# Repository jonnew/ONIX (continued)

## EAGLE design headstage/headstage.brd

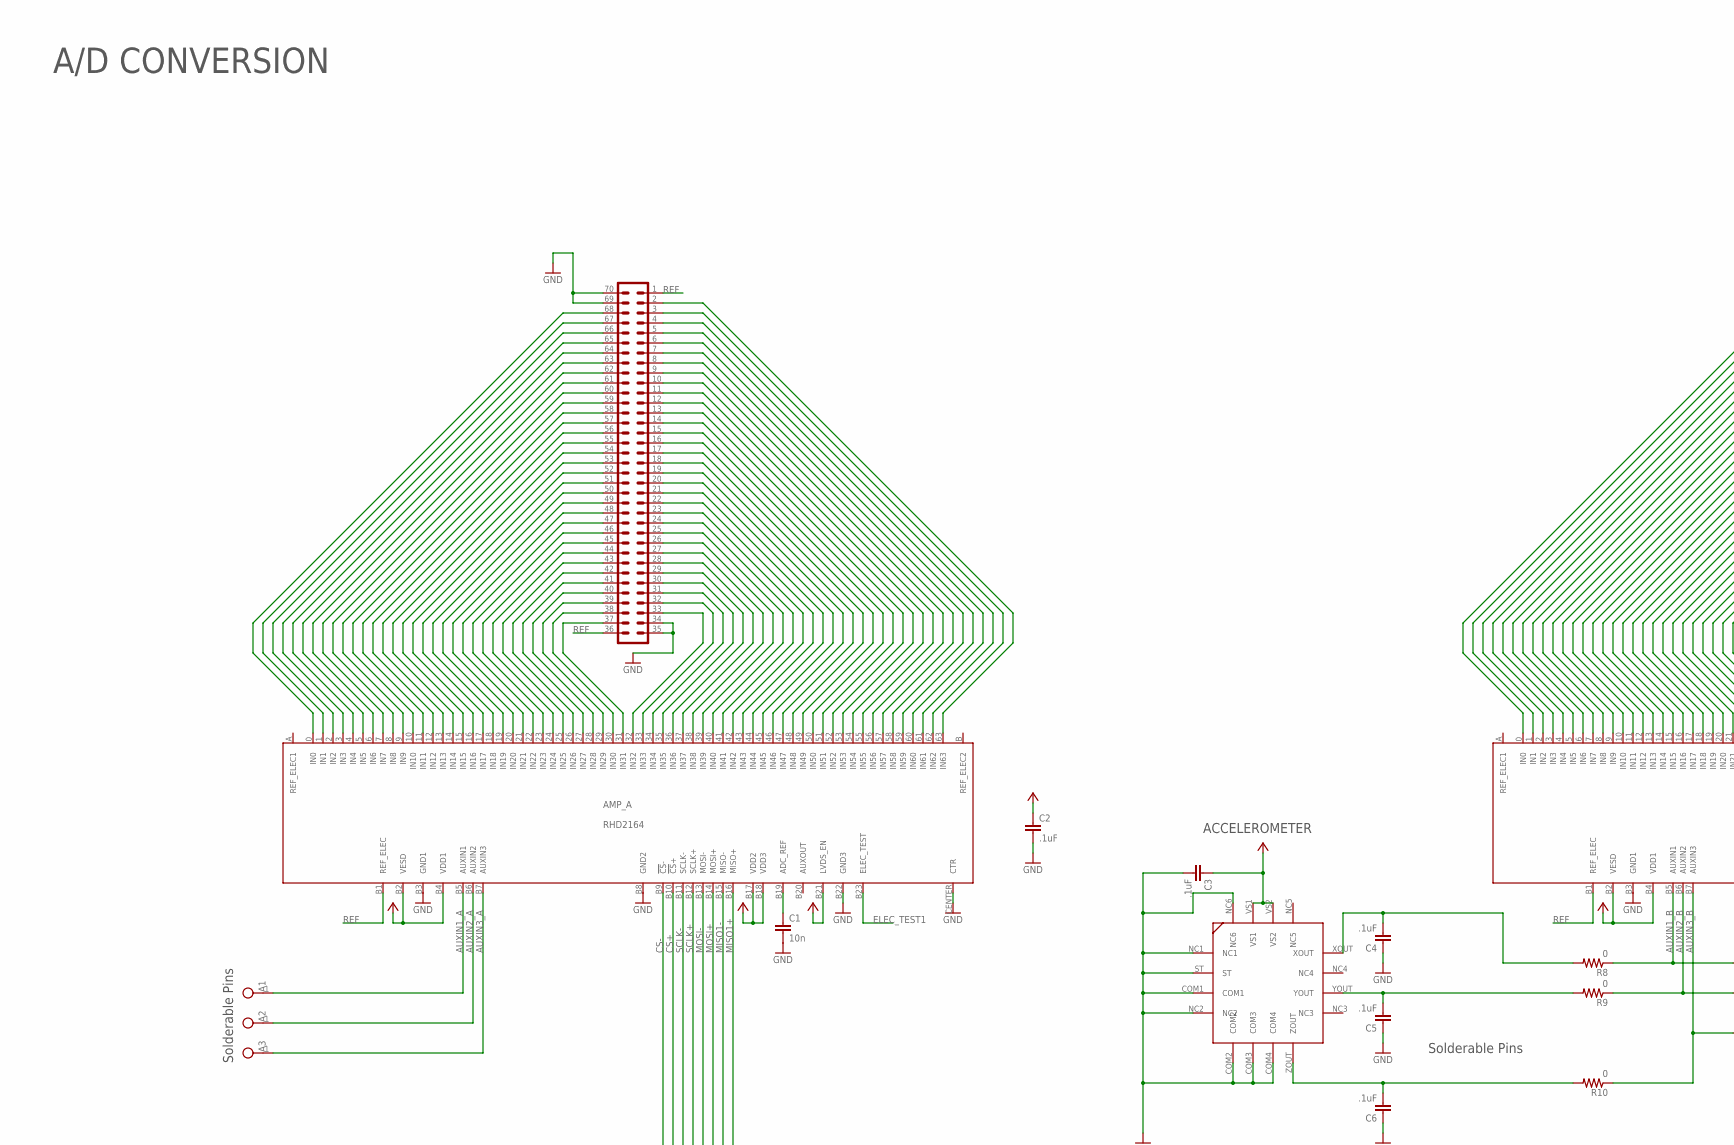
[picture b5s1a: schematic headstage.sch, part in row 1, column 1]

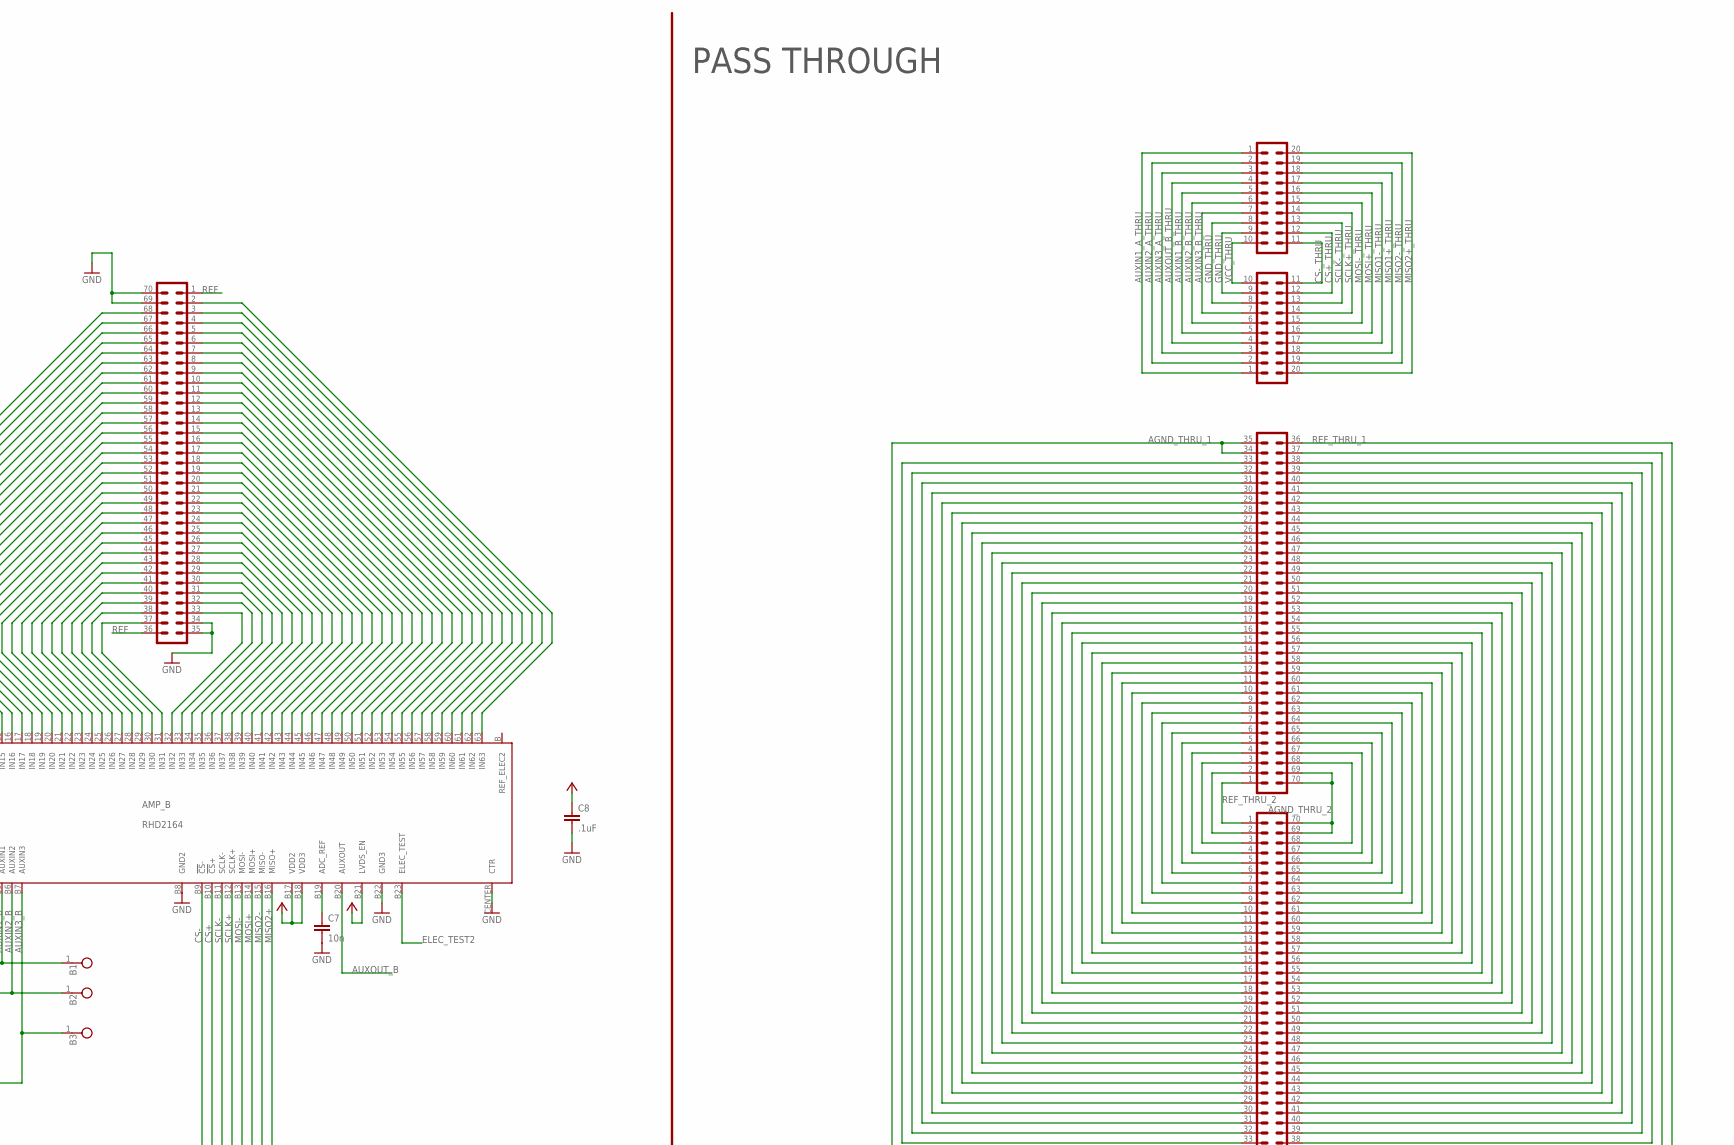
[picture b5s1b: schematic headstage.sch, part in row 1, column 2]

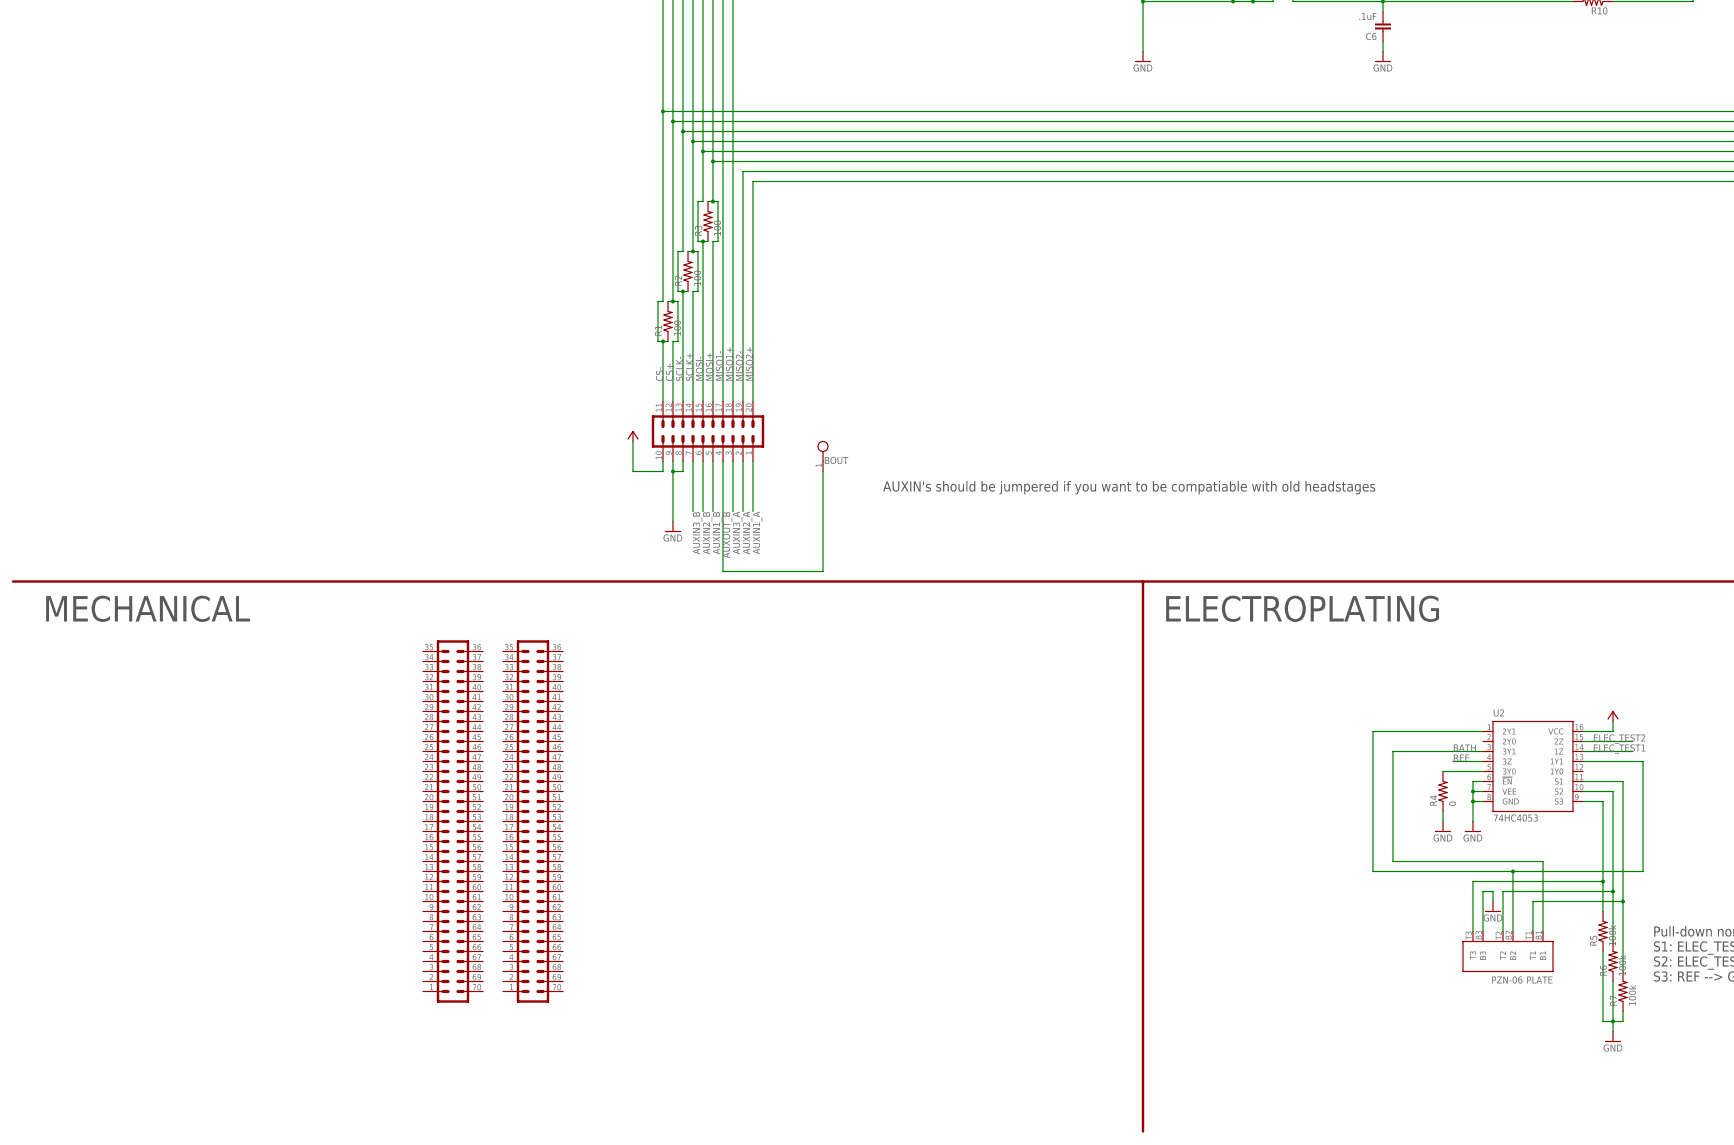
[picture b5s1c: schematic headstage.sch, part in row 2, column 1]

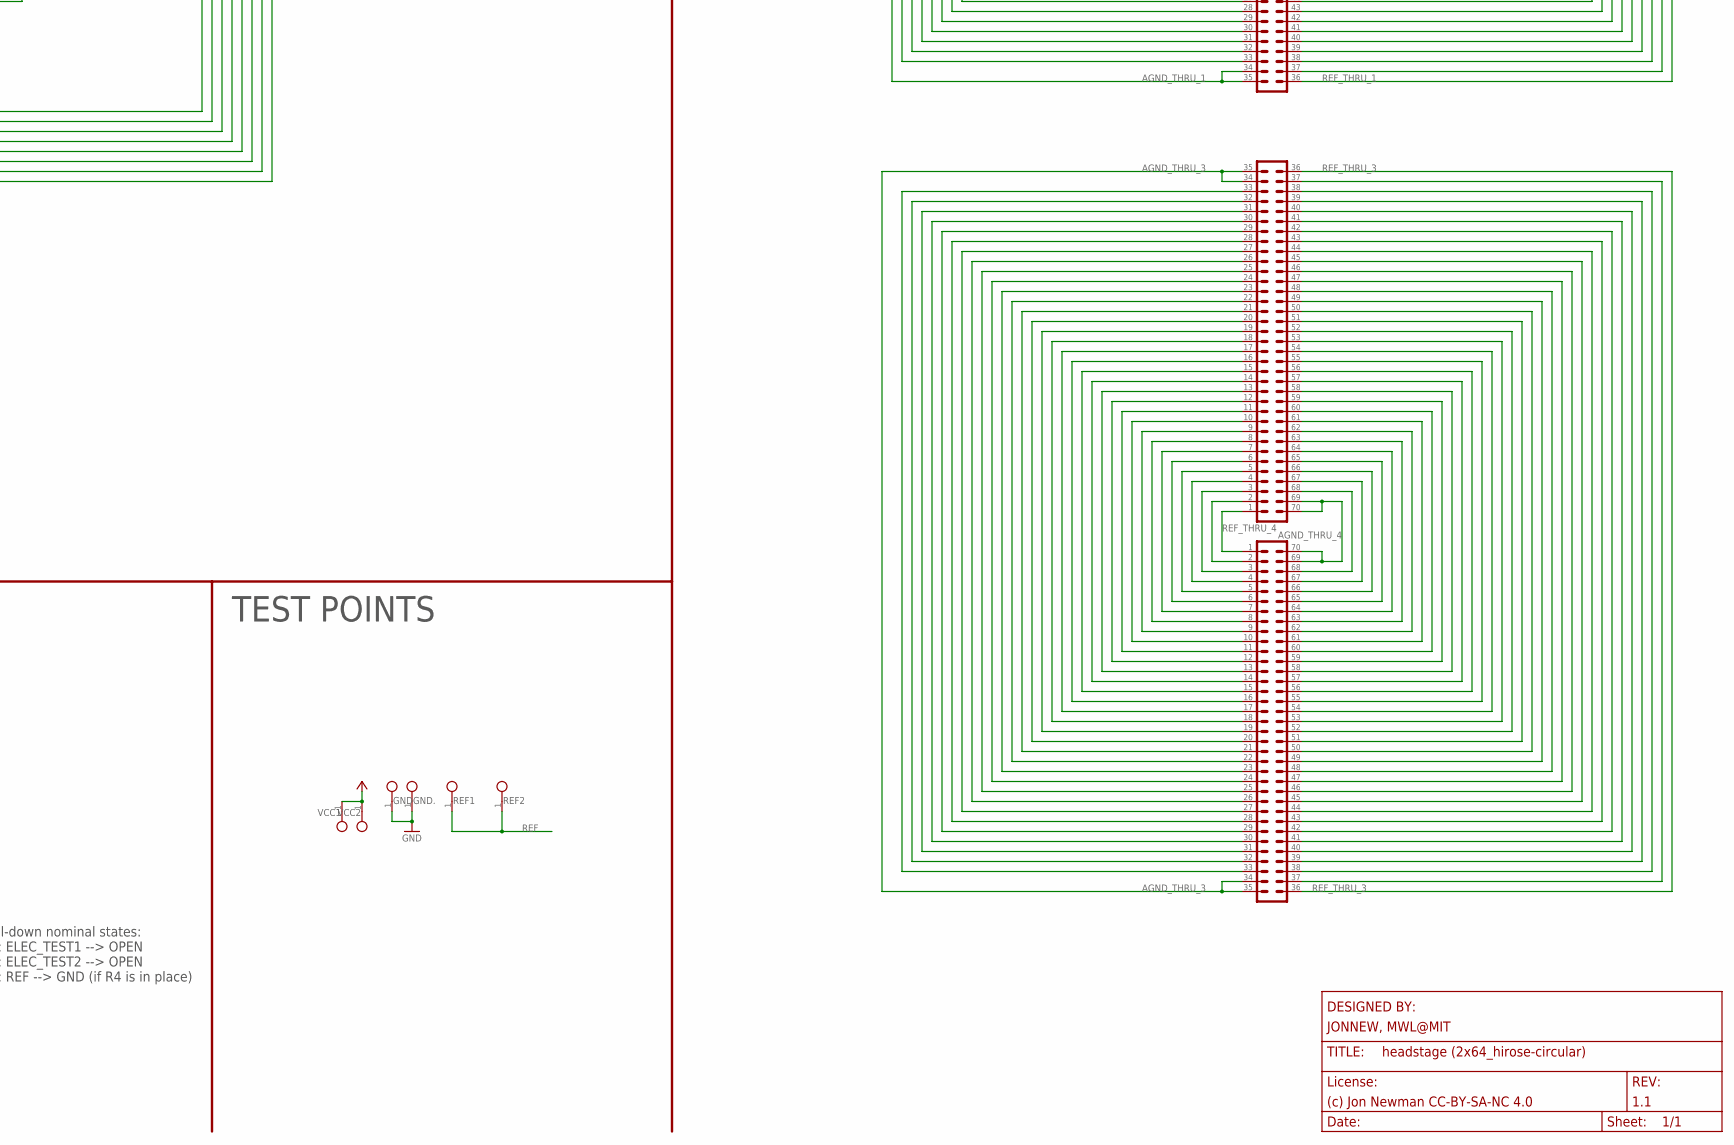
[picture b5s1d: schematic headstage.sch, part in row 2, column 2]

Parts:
A1, A2, A3: TESTPOINT_SMALL
AIN_BNB: DF40REC; DF40-70REC
AIN_BSB: DF40REC; DF40-70REC
AMP_A: RHD2164; RHD2164_COB
AMP_B: RHD2164; RHD2164_COB
ATHRU_BEB: DF40REC; DF40-70REC
ATHRU_BWB: DF40REC; DF40-70REC
ATHRU_TEB: DF40HEAD; DF40-70HEAD
ATHRU_TWB: DF40HEAD; DF40-70HEAD
B1, B2, B3: TESTPOINT_SMALL
BOUT: TESTPOINT_SMALL
C1, C7: 10n; 0201
C2, C3, C4, C5, C6, C8: .1uF; 0402
DIO_TEA: DF40HEAD; DF40-20HEAD
DTHRU_BNA: DF40REC; DF40-20REC
DTHRU_TNA: DF40HEAD; DF40-20HEAD
GND, GND.: GND; TESTPOINT_SMALL
MECH_TNB: DF40HEAD; DF40-70HEAD
MECH_TSB: DF40HEAD; DF40-70HEAD
PLATE: PZN-06; OMNETICS_PZN-06-AA
R1, R2, R3: 100; 0201
R4: 0; 0402
R5, R6, R7: 100k; 0201
R8, R9, R10: 0; 0201
REF1, REF2: REF; TESTPOINT_SMALL
U1: ADXL335
U2: 74HC4053; TSSOP-16
VCC1, VCC2: VCC; TESTPOINT_SMALL

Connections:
AGND_THRU_1: ATHRU_BWB.34, ATHRU_BWB.35, ATHRU_TWB.34, ATHRU_TWB.35
AGND_THRU_2: ATHRU_BWB.69, ATHRU_BWB.70, ATHRU_TWB.69, ATHRU_TWB.70
AGND_THRU_3: ATHRU_BEB.34, ATHRU_BEB.35, ATHRU_TEB.34, ATHRU_TEB.35
AGND_THRU_4: ATHRU_BEB.69, ATHRU_BEB.70, ATHRU_TEB.69, ATHRU_TEB.70
AUXIN1_A: A1.1, AMP_A.B5 (AUXIN1), DIO_TEA.1
AUXIN1_A_THRU: DTHRU_BNA.1, DTHRU_TNA.1
AUXIN1_B: AMP_B.B5 (AUXIN1), B1.1, DIO_TEA.5, R8.1
AUXIN1_B_THRU: DTHRU_BNA.5, DTHRU_TNA.5
AUXIN2_A: A2.1, AMP_A.B6 (AUXIN2), DIO_TEA.2
AUXIN2_A_THRU: DTHRU_BNA.2, DTHRU_TNA.2
AUXIN2_B: AMP_B.B6 (AUXIN2), B2.1, DIO_TEA.6, R9.1
AUXIN2_B_THRU: DTHRU_BNA.6, DTHRU_TNA.6
AUXIN3_A: A3.1, AMP_A.B7 (AUXIN3), DIO_TEA.3
AUXIN3_A_THRU: DTHRU_BNA.3, DTHRU_TNA.3
AUXIN3_B: AMP_B.B7 (AUXIN3), B3.1, DIO_TEA.7, R10.1
AUXIN3_B_THRU: DTHRU_BNA.7, DTHRU_TNA.7
AUXOUT_B: AMP_B.B20 (AUXOUT), BOUT.1, DIO_TEA.4
AUXOUT_B_THRU: DTHRU_BNA.4, DTHRU_TNA.4
BATH: PLATE.B1, U2.3 (3Y1)
CS+: AMP_A.B10 (!CS!+), AMP_B.B10 (!CS!+), DIO_TEA.12, R1.2
CS+_THRU: DTHRU_BNA.12, DTHRU_TNA.12
CS-: AMP_A.B9 (!CS!-), AMP_B.B9 (!CS!-), DIO_TEA.11, R1.1
CS-_THRU: DTHRU_BNA.11, DTHRU_TNA.11
ELEC_TEST1: AMP_A.B23 (ELEC_TEST), U2.14 (1Z)
ELEC_TEST2: AMP_B.B23 (ELEC_TEST), U2.15 (2Z)
GND: AIN_BNB.34, AIN_BNB.35, AIN_BNB.69, AIN_BNB.70, AIN_BSB.34, AIN_BSB.35, AIN_BSB.69, AIN_BSB.70, AMP_A.B3 (GND1), AMP_A.B8 (GND2), AMP_A.B22 (GND3), AMP_A.CENTER (CTR), AMP_B.B3 (GND1), AMP_B.B8 (GND2), AMP_B.B22 (GND3), AMP_B.CENTER (CTR), ATHRU_TEB.M1, ATHRU_TEB.M2, ATHRU_TEB.M3, ATHRU_TEB.M4, ATHRU_TWB.M1, ATHRU_TWB.M2, ATHRU_TWB.M3, ATHRU_TWB.M4, C1.2, C2.2, C3.2, C4.1, C5.1, C6.1, C7.2, C8.2, DIO_TEA.8, DIO_TEA.9, DIO_TEA.M1, DIO_TEA.M2, DIO_TEA.M3, DIO_TEA.M4, DTHRU_TNA.M1, DTHRU_TNA.M2, DTHRU_TNA.M3, DTHRU_TNA.M4, GND.1, GND..1, MECH_TNB.M1, MECH_TNB.M2, MECH_TNB.M3, MECH_TNB.M4, MECH_TSB.M1, MECH_TSB.M2, MECH_TSB.M3, MECH_TSB.M4, PLATE.B3, R4.1, R5.1, R6.1, R7.1, U1.COM1, U1.COM2, U1.COM3, U1.COM4, U1.NC1, U1.NC2, U1.NC6, U1.ST, U2.6 (!EN!), U2.7 (VEE), U2.8 (GND)
GND_THRU: DTHRU_BNA.8, DTHRU_BNA.9, DTHRU_TNA.8, DTHRU_TNA.9
MISO1+: AMP_A.B16 (MISO+), DIO_TEA.18
MISO1+_THRU: DTHRU_BNA.18, DTHRU_TNA.18
MISO1-: AMP_A.B15 (MISO-), DIO_TEA.17
MISO1-_THRU: DTHRU_BNA.17, DTHRU_TNA.17
MISO2+: AMP_B.B16 (MISO+), DIO_TEA.20
MISO2+_THRU: DTHRU_BNA.20, DTHRU_TNA.20
MISO2-: AMP_B.B15 (MISO-), DIO_TEA.19
MISO2-_THRU: DTHRU_BNA.19, DTHRU_TNA.19
MOSI+: AMP_A.B14 (MOSI+), AMP_B.B14 (MOSI+), DIO_TEA.16, R3.2
MOSI+_THRU: DTHRU_BNA.16, DTHRU_TNA.16
MOSI-: AMP_A.B13 (MOSI-), AMP_B.B13 (MOSI-), DIO_TEA.15, R3.1
MOSI-_THRU: DTHRU_BNA.15, DTHRU_TNA.15
unnamed: AMP_B.B19 (ADC_REF), C7.1
unnamed: AIN_BNB.38, AMP_A.30 (IN30)
unnamed: AIN_BNB.39, AMP_A.29 (IN29)
unnamed: AIN_BNB.40, AMP_A.28 (IN28)
unnamed: AIN_BNB.41, AMP_A.27 (IN27)
unnamed: AIN_BNB.42, AMP_A.26 (IN26)
unnamed: AIN_BNB.32, AMP_A.33 (IN33)
unnamed: AIN_BNB.31, AMP_A.34 (IN34)
unnamed: AIN_BNB.30, AMP_A.35 (IN35)
unnamed: AIN_BNB.29, AMP_A.36 (IN36)
unnamed: AIN_BSB.38, AMP_B.30 (IN30)
unnamed: AIN_BNB.28, AMP_A.37 (IN37)
unnamed: AIN_BNB.27, AMP_A.38 (IN38)
unnamed: AIN_BNB.26, AMP_A.39 (IN39)
unnamed: AIN_BNB.25, AMP_A.40 (IN40)
unnamed: AIN_BNB.24, AMP_A.41 (IN41)
unnamed: AIN_BNB.23, AMP_A.42 (IN42)
unnamed: AIN_BNB.22, AMP_A.43 (IN43)
unnamed: AIN_BNB.21, AMP_A.44 (IN44)
unnamed: AIN_BNB.20, AMP_A.45 (IN45)
unnamed: AIN_BNB.19, AMP_A.46 (IN46)
unnamed: AIN_BNB.18, AMP_A.47 (IN47)
unnamed: AIN_BNB.17, AMP_A.48 (IN48)
unnamed: AIN_BNB.16, AMP_A.49 (IN49)
unnamed: AIN_BNB.15, AMP_A.50 (IN50)
unnamed: AIN_BNB.14, AMP_A.51 (IN51)
unnamed: AIN_BNB.13, AMP_A.52 (IN52)
unnamed: AIN_BNB.12, AMP_A.53 (IN53)
unnamed: AIN_BNB.11, AMP_A.54 (IN54)
unnamed: AIN_BNB.10, AMP_A.55 (IN55)
unnamed: AIN_BNB.9, AMP_A.56 (IN56)
unnamed: AIN_BNB.8, AMP_A.57 (IN57)
unnamed: AIN_BNB.7, AMP_A.58 (IN58)
unnamed: AIN_BNB.6, AMP_A.59 (IN59)
unnamed: AIN_BSB.39, AMP_B.29 (IN29)
unnamed: AIN_BSB.40, AMP_B.28 (IN28)
unnamed: AIN_BSB.41, AMP_B.27 (IN27)
unnamed: AIN_BSB.42, AMP_B.26 (IN26)
unnamed: AIN_BSB.43, AMP_B.25 (IN25)
unnamed: AIN_BSB.44, AMP_B.24 (IN24)
unnamed: AIN_BNB.5, AMP_A.60 (IN60)
unnamed: AMP_A.B19 (ADC_REF), C1.1
unnamed: AIN_BNB.4, AMP_A.61 (IN61)
unnamed: AIN_BNB.3, AMP_A.62 (IN62)
unnamed: AIN_BNB.2, AMP_A.63 (IN63)
unnamed: AIN_BNB.33, AMP_A.32 (IN32)
unnamed: AIN_BSB.45, AMP_B.23 (IN23)
unnamed: AIN_BSB.46, AMP_B.22 (IN22)
unnamed: AIN_BSB.47, AMP_B.21 (IN21)
unnamed: AIN_BSB.48, AMP_B.20 (IN20)
unnamed: AIN_BSB.49, AMP_B.19 (IN19)
unnamed: AIN_BSB.50, AMP_B.18 (IN18)
unnamed: AIN_BSB.51, AMP_B.17 (IN17)
unnamed: AIN_BSB.52, AMP_B.16 (IN16)
unnamed: AIN_BSB.53, AMP_B.15 (IN15)
unnamed: AIN_BSB.54, AMP_B.14 (IN14)
unnamed: AIN_BSB.55, AMP_B.13 (IN13)
unnamed: AIN_BSB.56, AMP_B.12 (IN12)
unnamed: AIN_BSB.57, AMP_B.11 (IN11)
unnamed: AIN_BSB.58, AMP_B.10 (IN10)
unnamed: AIN_BSB.59, AMP_B.9 (IN9)
unnamed: AIN_BSB.60, AMP_B.8 (IN8)
unnamed: AIN_BSB.61, AMP_B.7 (IN7)
unnamed: AIN_BSB.62, AMP_B.6 (IN6)
unnamed: AIN_BSB.63, AMP_B.5 (IN5)
unnamed: AIN_BSB.64, AMP_B.4 (IN4)
unnamed: AIN_BSB.65, AMP_B.3 (IN3)
unnamed: AIN_BSB.66, AMP_B.2 (IN2)
unnamed: AIN_BSB.67, AMP_B.1 (IN1)
unnamed: AIN_BNB.43, AMP_A.25 (IN25)
unnamed: AIN_BNB.44, AMP_A.24 (IN24)
unnamed: AIN_BNB.45, AMP_A.23 (IN23)
unnamed: AIN_BNB.46, AMP_A.22 (IN22)
unnamed: AIN_BSB.68, AMP_B.0 (IN0)
unnamed: AIN_BSB.37, AMP_B.31 (IN31)
unnamed: AIN_BSB.32, AMP_B.33 (IN33)
unnamed: AIN_BSB.31, AMP_B.34 (IN34)
unnamed: AIN_BSB.30, AMP_B.35 (IN35)
unnamed: AIN_BSB.29, AMP_B.36 (IN36)
unnamed: AIN_BSB.28, AMP_B.37 (IN37)
unnamed: AIN_BSB.27, AMP_B.38 (IN38)
unnamed: AIN_BSB.26, AMP_B.39 (IN39)
unnamed: AIN_BSB.25, AMP_B.40 (IN40)
unnamed: AIN_BSB.24, AMP_B.41 (IN41)
unnamed: AIN_BSB.23, AMP_B.42 (IN42)
unnamed: AIN_BSB.22, AMP_B.43 (IN43)
unnamed: AIN_BSB.21, AMP_B.44 (IN44)
unnamed: AIN_BSB.20, AMP_B.45 (IN45)
unnamed: AIN_BSB.19, AMP_B.46 (IN46)
unnamed: AIN_BSB.18, AMP_B.47 (IN47)
unnamed: AIN_BSB.17, AMP_B.48 (IN48)
unnamed: AIN_BSB.16, AMP_B.49 (IN49)
unnamed: AIN_BSB.15, AMP_B.50 (IN50)
unnamed: AIN_BSB.14, AMP_B.51 (IN51)
unnamed: AIN_BSB.13, AMP_B.52 (IN52)
unnamed: AIN_BSB.12, AMP_B.53 (IN53)
unnamed: AIN_BSB.11, AMP_B.54 (IN54)
unnamed: AIN_BSB.10, AMP_B.55 (IN55)
unnamed: AIN_BSB.9, AMP_B.56 (IN56)
unnamed: AIN_BSB.8, AMP_B.57 (IN57)
unnamed: AIN_BSB.7, AMP_B.58 (IN58)
unnamed: AIN_BSB.6, AMP_B.59 (IN59)
unnamed: AIN_BSB.5, AMP_B.60 (IN60)
unnamed: AIN_BSB.4, AMP_B.61 (IN61)
unnamed: AIN_BSB.3, AMP_B.62 (IN62)
unnamed: AIN_BSB.2, AMP_B.63 (IN63)
unnamed: AIN_BSB.33, AMP_B.32 (IN32)
unnamed: ATHRU_BEB.33, ATHRU_TEB.33
unnamed: ATHRU_BEB.32, ATHRU_TEB.32
unnamed: ATHRU_BEB.31, ATHRU_TEB.31
unnamed: ATHRU_BEB.30, ATHRU_TEB.30
unnamed: ATHRU_BEB.29, ATHRU_TEB.29
unnamed: ATHRU_BEB.28, ATHRU_TEB.28
unnamed: ATHRU_BEB.27, ATHRU_TEB.27
unnamed: ATHRU_BEB.26, ATHRU_TEB.26
unnamed: ATHRU_BEB.25, ATHRU_TEB.25
unnamed: ATHRU_BEB.24, ATHRU_TEB.24
unnamed: ATHRU_BEB.23, ATHRU_TEB.23
unnamed: ATHRU_BEB.22, ATHRU_TEB.22
unnamed: ATHRU_BEB.21, ATHRU_TEB.21
unnamed: ATHRU_BEB.20, ATHRU_TEB.20
unnamed: ATHRU_BEB.19, ATHRU_TEB.19
unnamed: ATHRU_BEB.18, ATHRU_TEB.18
unnamed: ATHRU_BEB.17, ATHRU_TEB.17
unnamed: ATHRU_BEB.16, ATHRU_TEB.16
unnamed: ATHRU_BEB.15, ATHRU_TEB.15
unnamed: ATHRU_BEB.14, ATHRU_TEB.14
unnamed: ATHRU_BEB.13, ATHRU_TEB.13
unnamed: ATHRU_BEB.12, ATHRU_TEB.12
unnamed: ATHRU_BEB.11, ATHRU_TEB.11
unnamed: PLATE.T1, R7.2, U2.11 (S1)
unnamed: PLATE.T2, R6.2, U2.10 (S2)
unnamed: PLATE.T3, R5.2, U2.9 (S3)
unnamed: R4.2, U2.5 (3Y0)
unnamed: PLATE.B2, U2.1 (2Y1), U2.13 (1Y1)
unnamed: AIN_BNB.47, AMP_A.21 (IN21)
unnamed: AIN_BNB.48, AMP_A.20 (IN20)
unnamed: AIN_BNB.49, AMP_A.19 (IN19)
unnamed: AIN_BNB.50, AMP_A.18 (IN18)
unnamed: AIN_BNB.51, AMP_A.17 (IN17)
unnamed: AIN_BNB.52, AMP_A.16 (IN16)
unnamed: AIN_BNB.53, AMP_A.15 (IN15)
unnamed: AIN_BNB.54, AMP_A.14 (IN14)
unnamed: AIN_BNB.55, AMP_A.13 (IN13)
unnamed: AIN_BNB.56, AMP_A.12 (IN12)
unnamed: AIN_BNB.57, AMP_A.11 (IN11)
unnamed: AIN_BNB.58, AMP_A.10 (IN10)
unnamed: AIN_BNB.59, AMP_A.9 (IN9)
unnamed: AIN_BNB.60, AMP_A.8 (IN8)
unnamed: AIN_BNB.61, AMP_A.7 (IN7)
unnamed: AIN_BNB.62, AMP_A.6 (IN6)
unnamed: AIN_BNB.63, AMP_A.5 (IN5)
unnamed: AIN_BNB.64, AMP_A.4 (IN4)
unnamed: AIN_BNB.65, AMP_A.3 (IN3)
unnamed: AIN_BNB.66, AMP_A.2 (IN2)
unnamed: ATHRU_BEB.10, ATHRU_TEB.10
unnamed: ATHRU_BEB.9, ATHRU_TEB.9
unnamed: ATHRU_BEB.8, ATHRU_TEB.8
unnamed: ATHRU_BEB.7, ATHRU_TEB.7
unnamed: ATHRU_BEB.6, ATHRU_TEB.6
unnamed: AIN_BNB.37, AMP_A.31 (IN31)
unnamed: ATHRU_BEB.5, ATHRU_TEB.5
unnamed: ATHRU_BEB.4, ATHRU_TEB.4
unnamed: ATHRU_BEB.3, ATHRU_TEB.3
unnamed: ATHRU_BEB.2, ATHRU_TEB.2
unnamed: ATHRU_BEB.38, ATHRU_TEB.38
unnamed: ATHRU_BEB.39, ATHRU_TEB.39
unnamed: ATHRU_BEB.40, ATHRU_TEB.40
unnamed: ATHRU_BEB.41, ATHRU_TEB.41
unnamed: ATHRU_BEB.42, ATHRU_TEB.42
unnamed: ATHRU_BEB.43, ATHRU_TEB.43
unnamed: ATHRU_BEB.44, ATHRU_TEB.44
unnamed: ATHRU_BEB.45, ATHRU_TEB.45
unnamed: ATHRU_BEB.46, ATHRU_TEB.46
unnamed: ATHRU_BEB.47, ATHRU_TEB.47
unnamed: ATHRU_BEB.48, ATHRU_TEB.48
unnamed: ATHRU_BEB.49, ATHRU_TEB.49
unnamed: ATHRU_BEB.50, ATHRU_TEB.50
unnamed: ATHRU_BEB.51, ATHRU_TEB.51
unnamed: ATHRU_BEB.52, ATHRU_TEB.52
unnamed: ATHRU_BEB.53, ATHRU_TEB.53
unnamed: ATHRU_BEB.54, ATHRU_TEB.54
unnamed: ATHRU_BEB.55, ATHRU_TEB.55
unnamed: ATHRU_BEB.56, ATHRU_TEB.56
unnamed: ATHRU_BEB.57, ATHRU_TEB.57
unnamed: ATHRU_BEB.58, ATHRU_TEB.58
unnamed: ATHRU_BEB.59, ATHRU_TEB.59
unnamed: ATHRU_BEB.60, ATHRU_TEB.60
unnamed: ATHRU_BEB.61, ATHRU_TEB.61
unnamed: ATHRU_BEB.62, ATHRU_TEB.62
unnamed: ATHRU_BEB.63, ATHRU_TEB.63
unnamed: ATHRU_BEB.64, ATHRU_TEB.64
unnamed: ATHRU_BEB.65, ATHRU_TEB.65
unnamed: ATHRU_BEB.66, ATHRU_TEB.66
unnamed: ATHRU_BEB.67, ATHRU_TEB.67
unnamed: ATHRU_BEB.68, ATHRU_TEB.68
unnamed: ATHRU_BWB.33, ATHRU_TWB.33
unnamed: ATHRU_BWB.32, ATHRU_TWB.32
unnamed: ATHRU_BWB.31, ATHRU_TWB.31
unnamed: ATHRU_BWB.30, ATHRU_TWB.30
unnamed: ATHRU_BWB.29, ATHRU_TWB.29
unnamed: ATHRU_BWB.28, ATHRU_TWB.28
unnamed: ATHRU_BWB.27, ATHRU_TWB.27
unnamed: ATHRU_BWB.26, ATHRU_TWB.26
unnamed: ATHRU_BWB.25, ATHRU_TWB.25
unnamed: ATHRU_BWB.24, ATHRU_TWB.24
unnamed: ATHRU_BWB.23, ATHRU_TWB.23
unnamed: ATHRU_BWB.22, ATHRU_TWB.22
unnamed: ATHRU_BWB.21, ATHRU_TWB.21
unnamed: ATHRU_BWB.20, ATHRU_TWB.20
unnamed: ATHRU_BWB.19, ATHRU_TWB.19
unnamed: ATHRU_BWB.18, ATHRU_TWB.18
unnamed: ATHRU_BWB.17, ATHRU_TWB.17
unnamed: ATHRU_BWB.16, ATHRU_TWB.16
unnamed: ATHRU_BWB.15, ATHRU_TWB.15
unnamed: ATHRU_BWB.14, ATHRU_TWB.14
unnamed: ATHRU_BWB.13, ATHRU_TWB.13
unnamed: ATHRU_BWB.12, ATHRU_TWB.12
unnamed: ATHRU_BWB.11, ATHRU_TWB.11
unnamed: ATHRU_BWB.10, ATHRU_TWB.10
unnamed: ATHRU_BWB.9, ATHRU_TWB.9
unnamed: ATHRU_BWB.8, ATHRU_TWB.8
unnamed: ATHRU_BWB.7, ATHRU_TWB.7
unnamed: ATHRU_BWB.6, ATHRU_TWB.6
unnamed: ATHRU_BWB.5, ATHRU_TWB.5
unnamed: ATHRU_BWB.4, ATHRU_TWB.4
unnamed: ATHRU_BWB.3, ATHRU_TWB.3
unnamed: ATHRU_BWB.2, ATHRU_TWB.2
unnamed: ATHRU_BWB.38, ATHRU_TWB.38
unnamed: ATHRU_BWB.39, ATHRU_TWB.39
unnamed: ATHRU_BWB.40, ATHRU_TWB.40
unnamed: ATHRU_BWB.41, ATHRU_TWB.41
unnamed: ATHRU_BWB.42, ATHRU_TWB.42
unnamed: ATHRU_BWB.43, ATHRU_TWB.43
unnamed: ATHRU_BWB.44, ATHRU_TWB.44
unnamed: ATHRU_BWB.45, ATHRU_TWB.45
unnamed: ATHRU_BWB.46, ATHRU_TWB.46
unnamed: ATHRU_BWB.47, ATHRU_TWB.47
unnamed: ATHRU_BWB.48, ATHRU_TWB.48
unnamed: ATHRU_BWB.49, ATHRU_TWB.49
unnamed: ATHRU_BWB.50, ATHRU_TWB.50
unnamed: ATHRU_BWB.51, ATHRU_TWB.51
unnamed: ATHRU_BWB.52, ATHRU_TWB.52
unnamed: ATHRU_BWB.53, ATHRU_TWB.53
unnamed: ATHRU_BWB.54, ATHRU_TWB.54
unnamed: ATHRU_BWB.55, ATHRU_TWB.55
unnamed: ATHRU_BWB.56, ATHRU_TWB.56
unnamed: ATHRU_BWB.57, ATHRU_TWB.57
unnamed: ATHRU_BWB.58, ATHRU_TWB.58
unnamed: ATHRU_BWB.59, ATHRU_TWB.59
unnamed: ATHRU_BWB.60, ATHRU_TWB.60
unnamed: ATHRU_BWB.61, ATHRU_TWB.61
unnamed: ATHRU_BWB.62, ATHRU_TWB.62
unnamed: ATHRU_BWB.63, ATHRU_TWB.63
unnamed: ATHRU_BWB.64, ATHRU_TWB.64
unnamed: ATHRU_BWB.65, ATHRU_TWB.65
unnamed: ATHRU_BWB.66, ATHRU_TWB.66
unnamed: ATHRU_BWB.67, ATHRU_TWB.67
unnamed: ATHRU_BWB.68, ATHRU_TWB.68
unnamed: ATHRU_BEB.37, ATHRU_TEB.37
unnamed: AIN_BNB.68, AMP_A.0 (IN0)
unnamed: AIN_BNB.67, AMP_A.1 (IN1)
unnamed: ATHRU_BWB.37, ATHRU_TWB.37
REF: AIN_BNB.1, AIN_BNB.36, AIN_BSB.1, AIN_BSB.36, AMP_A.B1 (REF_ELEC), AMP_B.B1 (REF_ELEC), REF1.1, REF2.1, U2.4 (3Z)
REF_THRU_1: ATHRU_BWB.36, ATHRU_TWB.36
REF_THRU_2: ATHRU_BWB.1, ATHRU_TWB.1
REF_THRU_3: ATHRU_BEB.36, ATHRU_TEB.36
REF_THRU_4: ATHRU_BEB.1, ATHRU_TEB.1
SCLK+: AMP_A.B12 (SCLK+), AMP_B.B12 (SCLK+), DIO_TEA.14, R2.2
SCLK+_THRU: DTHRU_BNA.14, DTHRU_TNA.14
SCLK-: AMP_A.B11 (SCLK-), AMP_B.B11 (SCLK-), DIO_TEA.13, R2.1
SCLK-_THRU: DTHRU_BNA.13, DTHRU_TNA.13
VCC: AMP_A.B2 (VESD), AMP_A.B4 (VDD1), AMP_A.B17 (VDD2), AMP_A.B18 (VDD3), AMP_A.B21 (LVDS_EN), AMP_B.B2 (VESD), AMP_B.B4 (VDD1), AMP_B.B17 (VDD2), AMP_B.B18 (VDD3), AMP_B.B21 (LVDS_EN), C2.1, C3.1, C8.1, DIO_TEA.10, U1.VS1, U1.VS2, U2.16 (VCC), VCC1.1, VCC2.1
VCC_THRU: DTHRU_BNA.10, DTHRU_TNA.10
XOUT1: C4.2, R8.2, U1.XOUT
YOUT1: C5.2, R9.2, U1.YOUT
ZOUT1: C6.2, R10.2, U1.ZOUT

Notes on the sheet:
MECHANICAL
ELECTROPLATING
A/D CONVERSION
PASS THROUGH
TEST POINTS
Pull-down nominal states: S1: ELEC_TEST1 --> OPEN S2: ELEC_TEST2 --> OPEN S3: REF --> GND (if R4 is in place)
Solderable Pins
AUXIN's should be jumpered if you want to be compatiable with old headstages
ACCELEROMETER

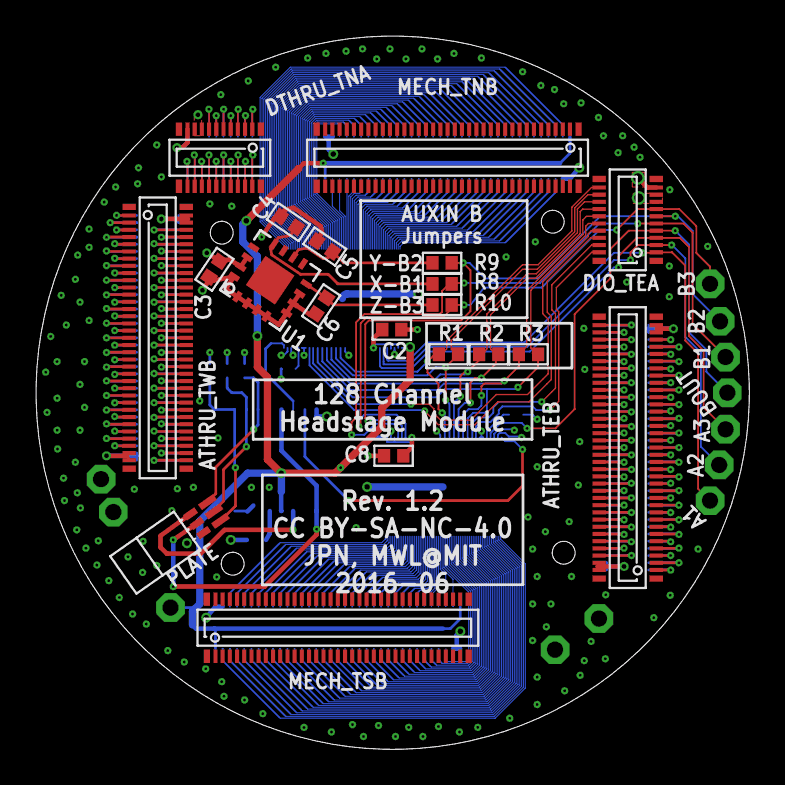
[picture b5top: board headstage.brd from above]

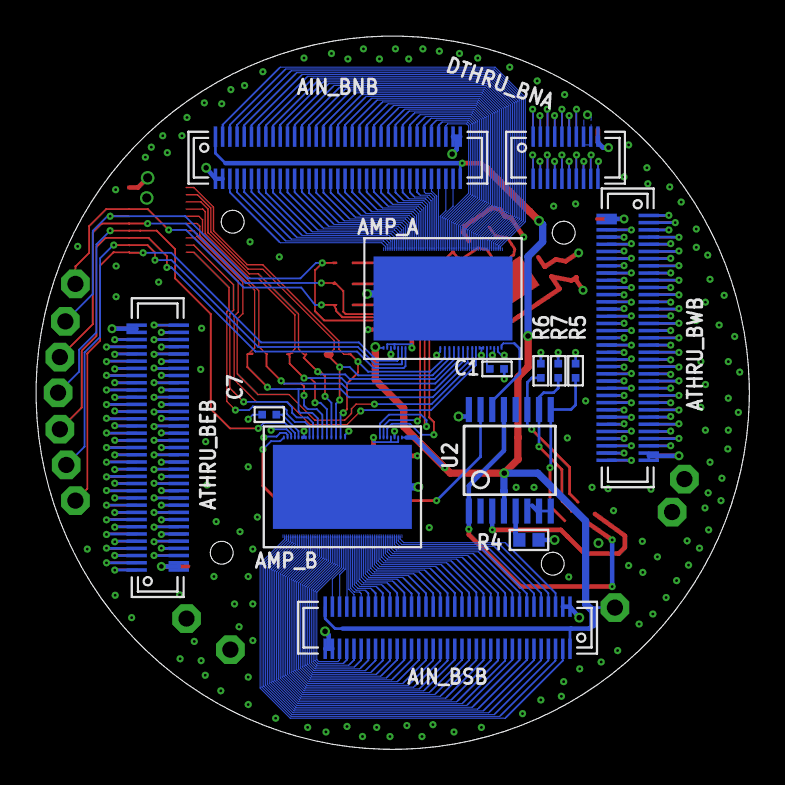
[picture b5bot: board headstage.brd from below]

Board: 4 copper layers, 39.6 x 39.6 mm, 46 parts (14 on the bottom side), 316 nets.
